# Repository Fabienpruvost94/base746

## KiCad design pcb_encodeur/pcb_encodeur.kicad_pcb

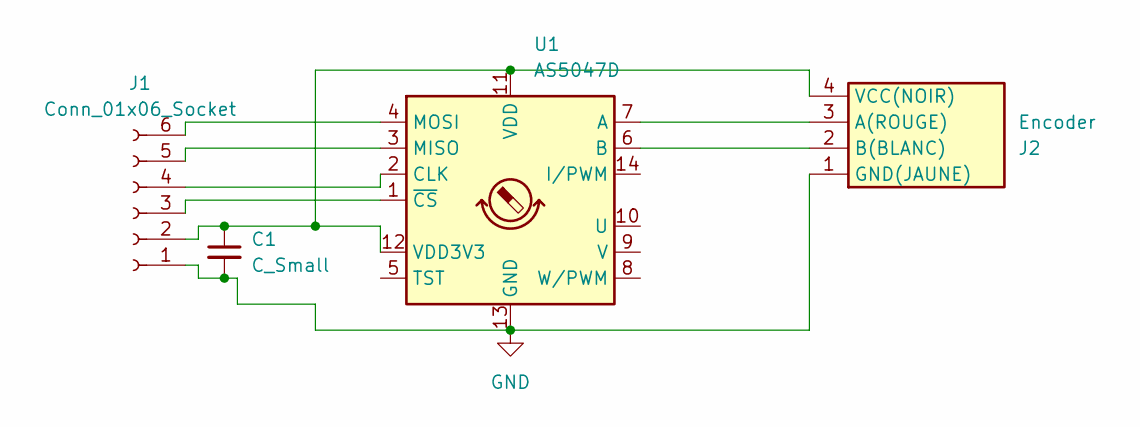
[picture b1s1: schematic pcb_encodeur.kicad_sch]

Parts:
C1: C_Small; C_0805_2012Metric
J1: Conn_01x06_Socket; PinHeader_1x06_P2.54mm_Vertical
J2: Encoder; SEEED_110990037
U1: AS5047D; TSSOP-14_4.4x5mm_P0.65mm

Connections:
GND: C1.2, J1.1, J2.1 (GND(JAUNE)), U1.13 (GND)
unnamed: C1.1, J1.2, J2.4 (VCC(NOIR)), U1.11 (VDD), U1.12 (VDD3V3)
unnamed: J1.3, U1.1 (~CS)
unnamed: J1.4, U1.2 (CLK)
unnamed: J1.5, U1.3 (MISO)
unnamed: J1.6, U1.4 (MOSI)
unnamed: J2.3 (A(ROUGE)), U1.7 (A)
unnamed: J2.2 (B(BLANC)), U1.6 (B)

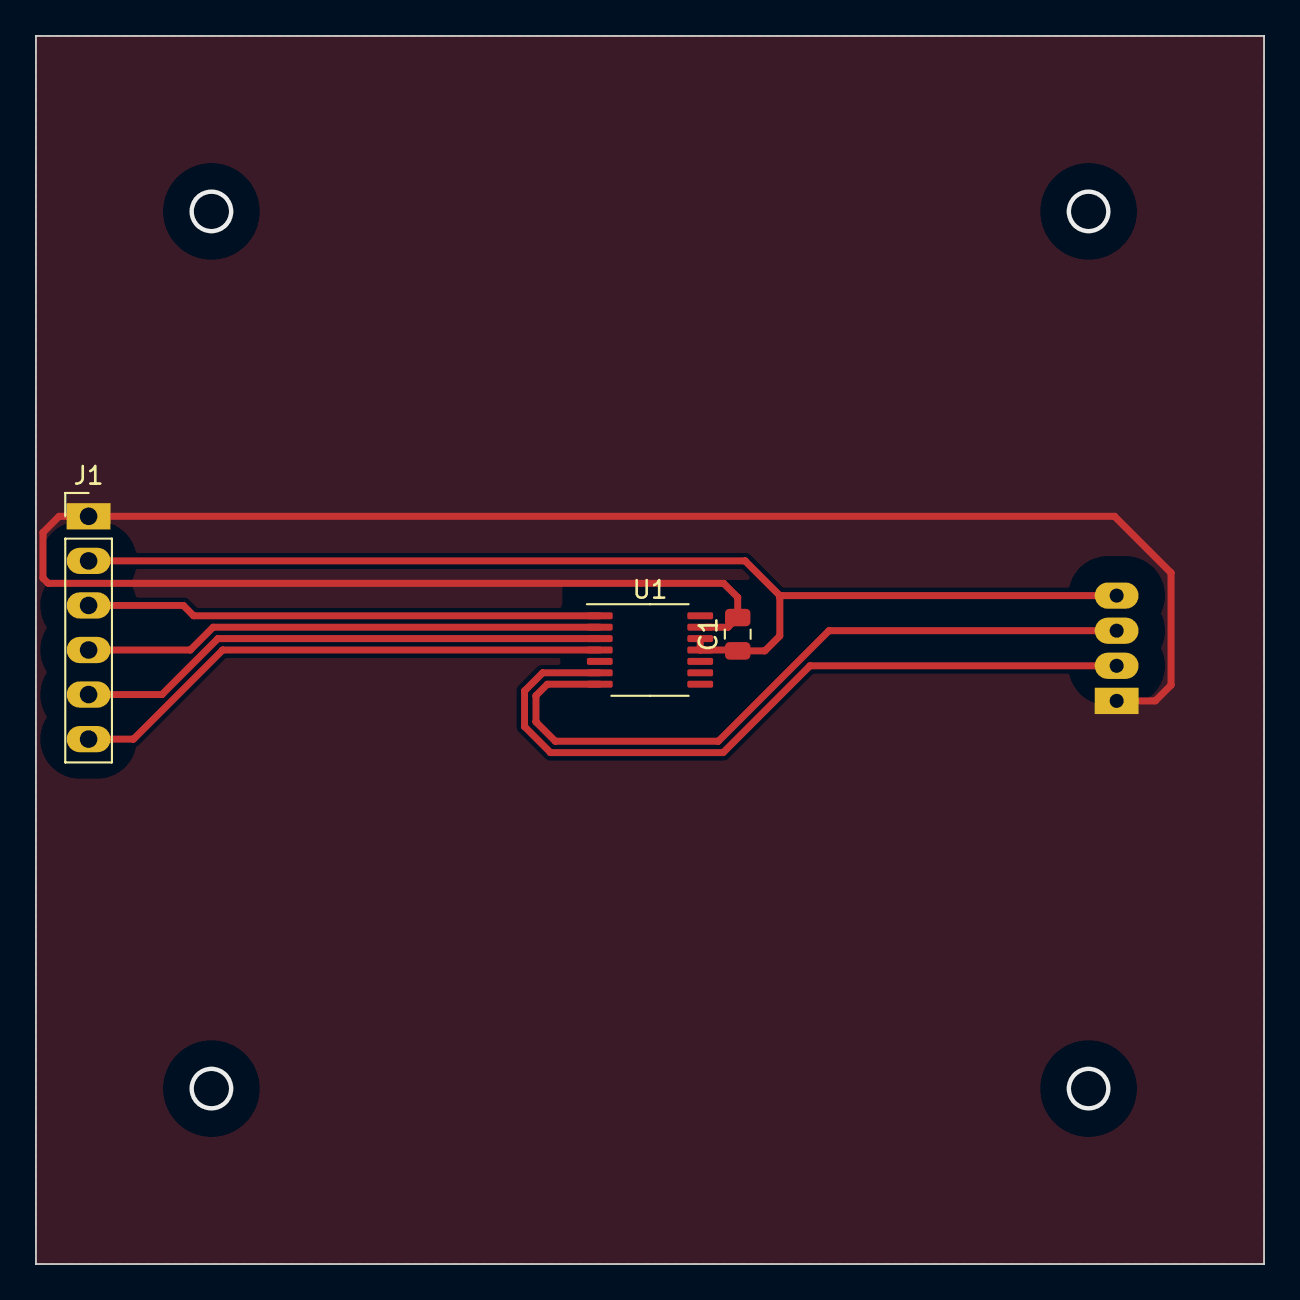
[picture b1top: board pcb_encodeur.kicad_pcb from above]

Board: 2 copper layers, 70.0 x 70.0 mm, 4 parts (1 on the bottom side), 8 nets.

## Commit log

2026-06-03 test
2026-06-03 coucou
2026-06-03 roulette 5 numero
2026-06-03 roulette 5 numeros V2
2026-06-04 ajout solde
2026-06-04 solde et gain modifiable
2026-06-09 version avec bouton de mise fonctionnelle
2026-06-09 affichage mieux avec bouton mises fonctionelles
2026-06-11 version avec mise fonctionnel
2026-06-11 fleche en image
2026-06-15 version finale pour présentation
2026-06-18 version commenter
2026-06-18 kicad en +
